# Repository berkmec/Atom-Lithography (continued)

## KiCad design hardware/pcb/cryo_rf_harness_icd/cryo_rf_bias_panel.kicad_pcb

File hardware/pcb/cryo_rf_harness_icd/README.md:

# Cryo-RF, Microwave, Quench & rf-SET Harness ICD (`hardware/pcb/cryo_rf_harness_icd/`)

> **Epistemic Status:** `M0_M1_DESIGN_ONLY` (`no_lab_measurement=true`, `no_physical_fab=true`, `iec61508_certified=false`, `semi_s2_certified=false`). All SPICE results below were executed live on rootless `ngspice-47`.

## 1. Scope (`17 E2` Parts + `S6.3-04` Quench Harness)
- **E2 Parts (`17`):** `S3.2-04, S6.4-03, S6.5-03, S6.6-01, S6.6-02, S6.6-03, S6.6-04, S6.6-07, S6.7-01, S6.10-01, S6.11-02, S6.11-03, S6.11-04, S9.3-02, S9.4-01, S9.4-02, S9.4-03`
- **Magnet Quench Harness (`1`):** `S6.3-04` (with `S7.SAFETY-05` external `1.563 Ohm` dump bank)

## 2. KiCad 8 Bulkhead Distribution PCB (`cryo_rf_bias_panel`)
- **Stackup:** 4-layer Rogers RO4350B (`er=3.48`, `0.254 mm` outer cores), `170 x 120 mm`
- **Verification:** **`0` ERC errors**, **`0` ERC warnings**, **`0` DRC errors**, SCH/PCB parity = **`True`**, **`routed_net_count = 67/67`**, **`unrouted_net_count = 0`**, **`unconnected_items = 0`**, **`track_dangling_count = 0`** (`316` segments, `95` vias)
- **Contents:** `115` components, `67` nets: `8x` 4 K InP HEMT bias channels, `4x` 20 mK TWPA flux-bias + Eccosorb CR-124 LPF lanes, `4x` `50.00 Ohm` controlled-impedance Rogers RO4350B RF/rf-SET bias-tee monitor lanes (`8` Z0 checks PASS), and `S6.3-04` `400 V` quench voltage-tap isolation bay protected by a `2.5 x 92 mm` milled `Edge.Cuts` air-slot (`1` HV checks PASS).

## 3. Live `ngspice-47` Simulation Verification
| Deck | BOM ID | Key Measured Metrics | Cross-Check Parity | Verdict |
|---|---|---|---|---|
| `qram_chebyshev_50_to_3k.cir` | `S9.4-02` | `max |S11|(4-8 GHz) = -24.4482 dB` (`<= -20 dB`), `min |S21| = -0.016282 dB` (`> -0.2 dB`), `BW(-20 dB) = 4.5181 GHz` (`3.7412-8.2592 GHz`) | Exact ABCD `|dS11| = 0.0 dB` | **PASS** |
| `magnet_quench_dump_1p563ohm.cir` | `S6.3-04` | `V_peak = 398.746 V` (`<= 400 V`), `tau = 0.37023 s` (`~0.370 s`), `E_dump = 18.8243 / 18.9408 kJ` (**`99.385% >= 99%`**), `T_dump_peak = 38.06 C` | Analytical LR `|dtau| = 0.011%` | **PASS** |
| `rf_set_tank_biastee.cir` | `S6.7-01` | `f_res = 321.0 MHz` (`250-400 MHz`), `|Gamma(50k)| = 0.07782`, `|Gamma(200k)| = 0.48068`, `Delta|Gamma| = 0.40286`, DC-bias RF isolation = **`113.57 dB`** (worst `200-450 MHz`: `98.69 dB > 40 dB`) | Python MNA `|dGamma| = 0.0` | **PASS** |

## 4. 6-Stage Thermal & Attenuation Reconciliation (`Exp125` / `Exp140` / `Exp142`)
- **Staged RF Input Attenuation:** `-20 dB (4 K) / -10 dB (800 mK Still) / -10 dB (100 mK CP) / -20 dB (20 mK MXC)` (`-60 dB` total, cascaded `n_th(6 GHz, 20 mK) = 0.00505`).
- **Combined M4 `1,024`-Cell (`Exp140`) + Option-Q (`Exp142`) Cryo Loads:**
  - `20 mK (MXC)`: **`7.036 uW`** (`<= 14.0 uW` LD400 cap)
  - `100 mK (CP)`: **`65.73 uW`** (`<= 400.0 uW` cap)
  - `800 mK (Still)`: **`1.09 mW`** (`<= 40.0 mW` cap)
  - `4 K`: **`0.55 W`** (`<= 2.0 W` PT420 cap)
  - `50 K`: **`8.74 W`** (`<= 40.0 W` / `55.0 W` PT420 cap)

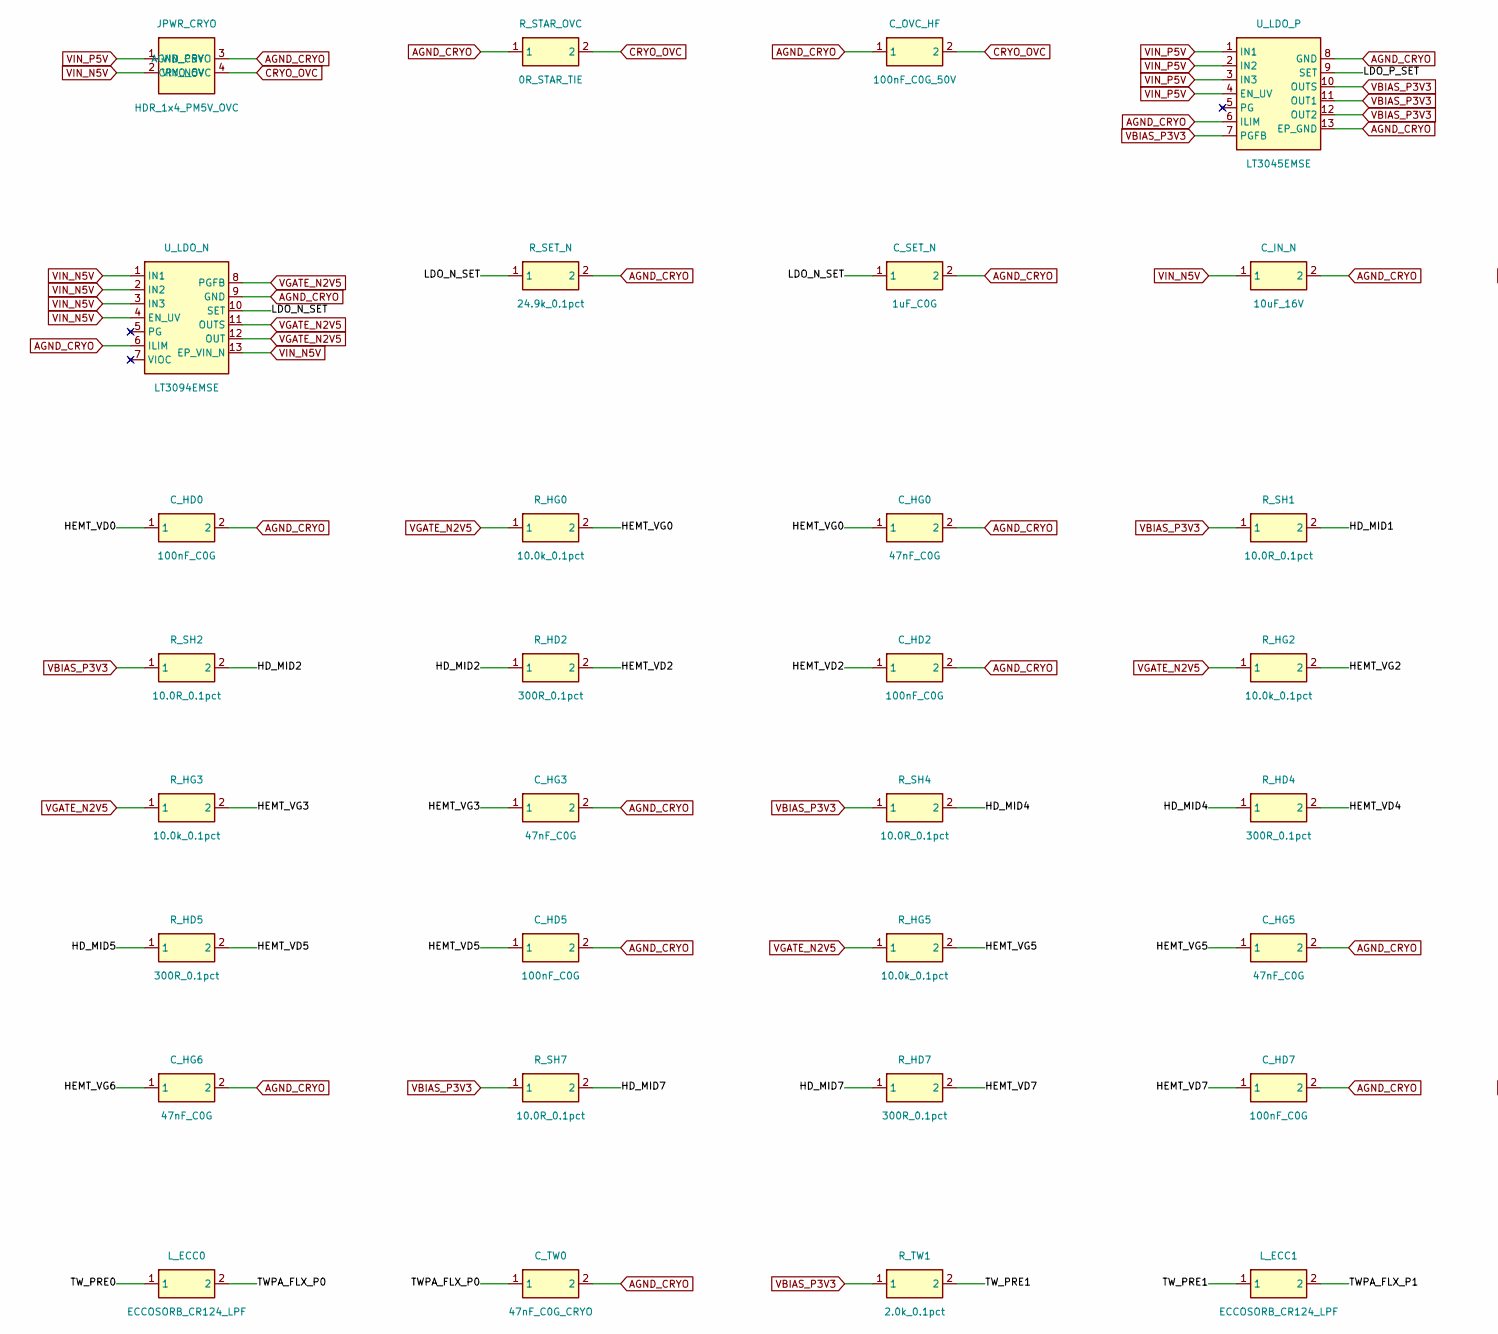
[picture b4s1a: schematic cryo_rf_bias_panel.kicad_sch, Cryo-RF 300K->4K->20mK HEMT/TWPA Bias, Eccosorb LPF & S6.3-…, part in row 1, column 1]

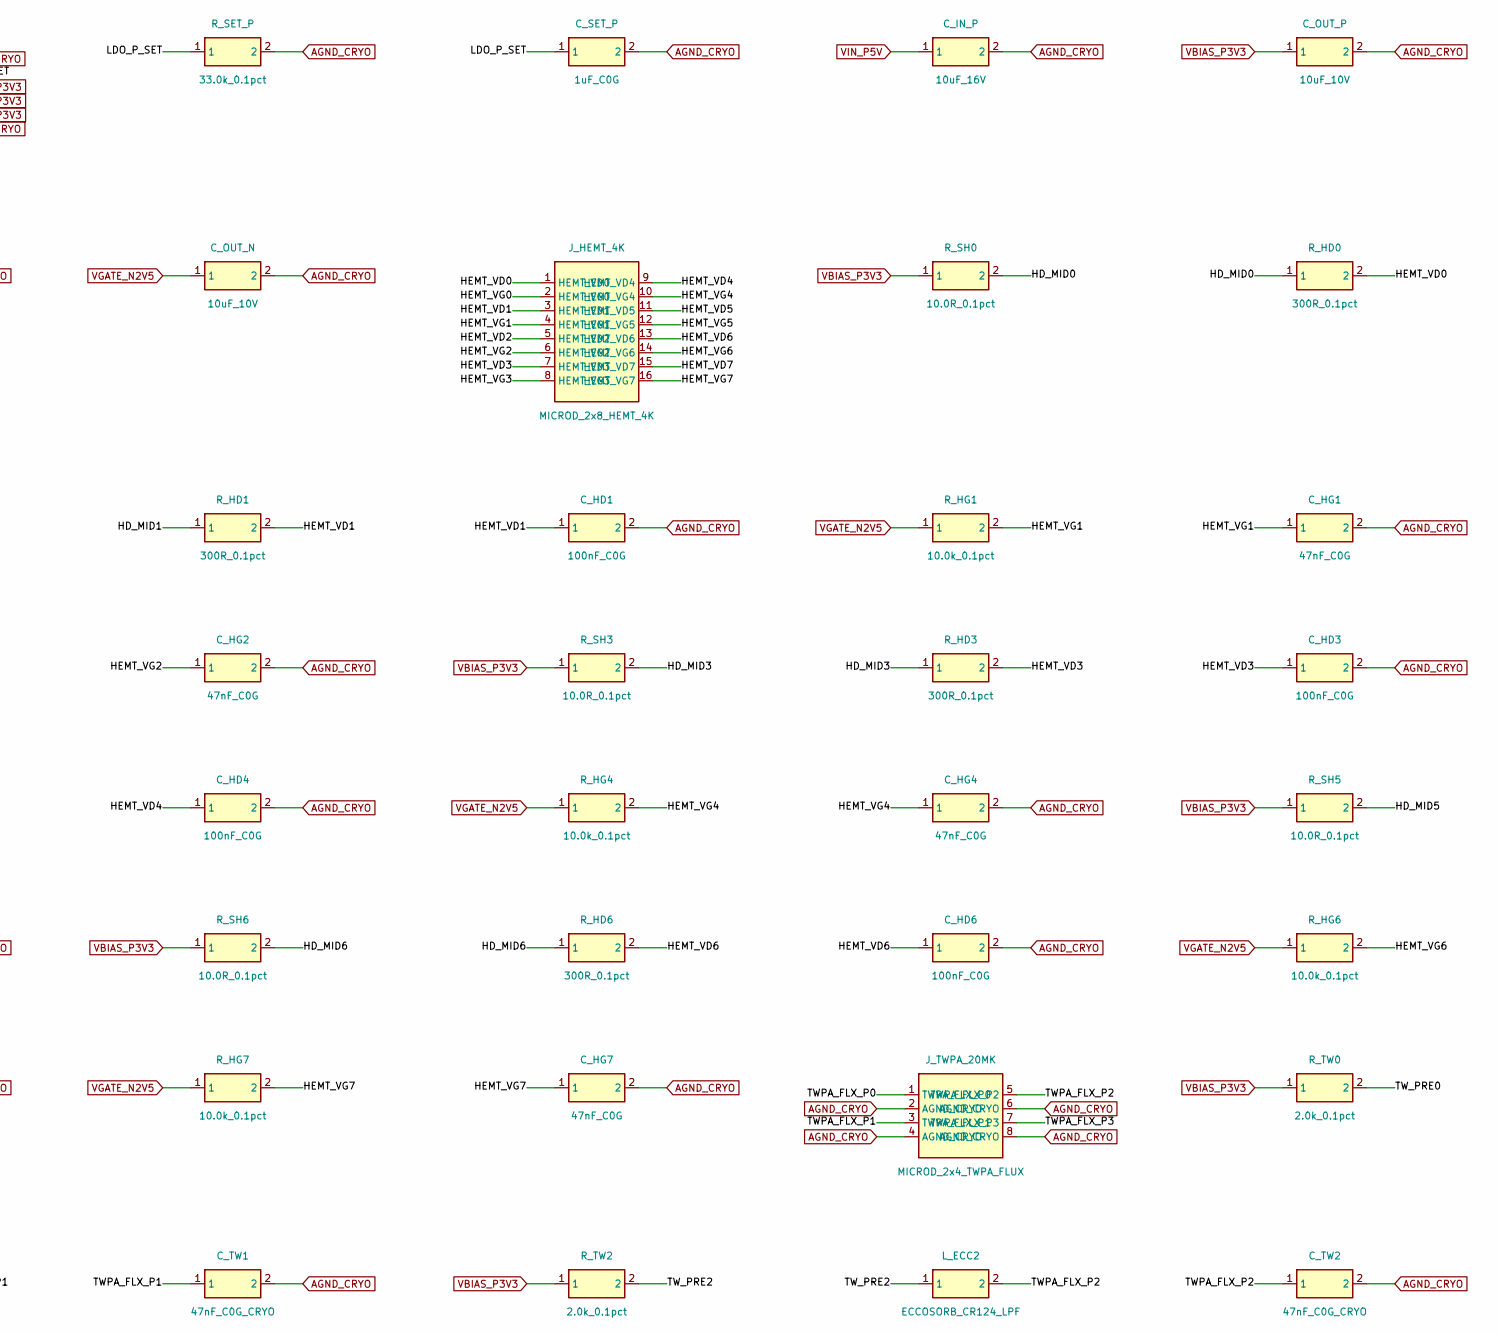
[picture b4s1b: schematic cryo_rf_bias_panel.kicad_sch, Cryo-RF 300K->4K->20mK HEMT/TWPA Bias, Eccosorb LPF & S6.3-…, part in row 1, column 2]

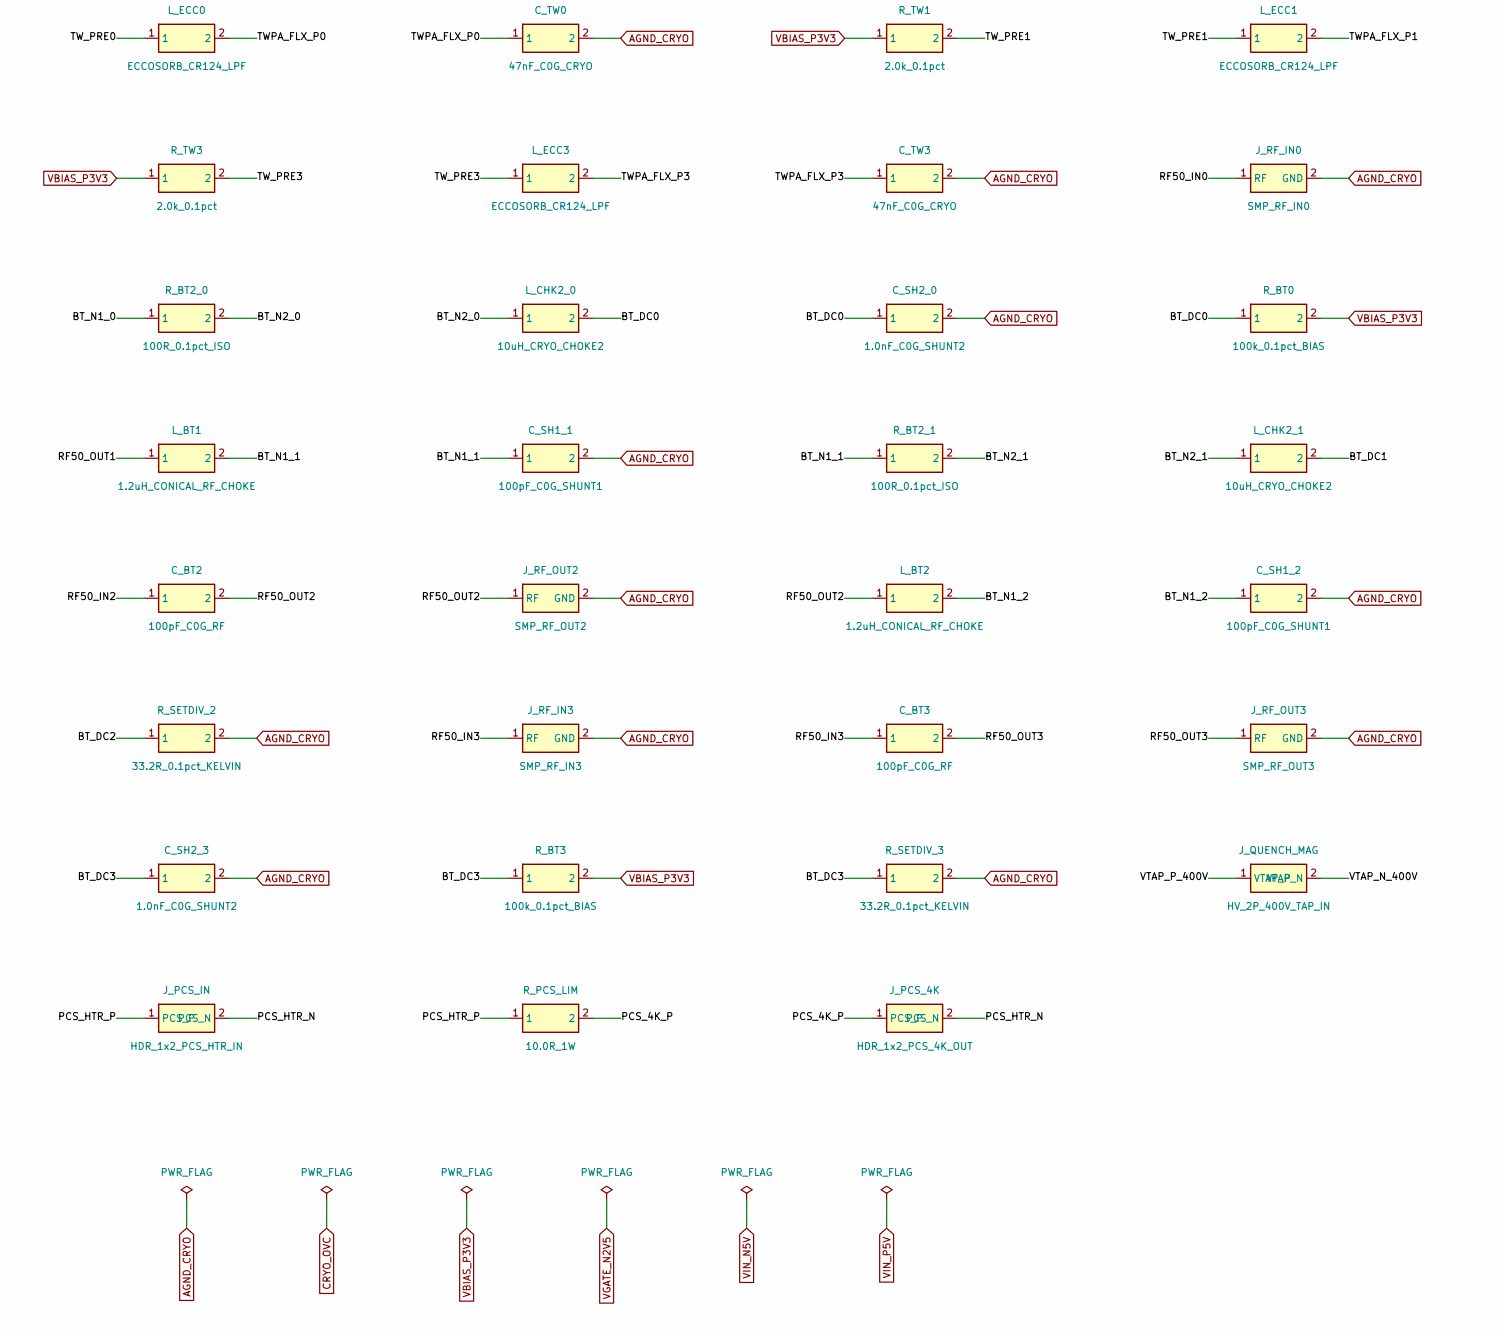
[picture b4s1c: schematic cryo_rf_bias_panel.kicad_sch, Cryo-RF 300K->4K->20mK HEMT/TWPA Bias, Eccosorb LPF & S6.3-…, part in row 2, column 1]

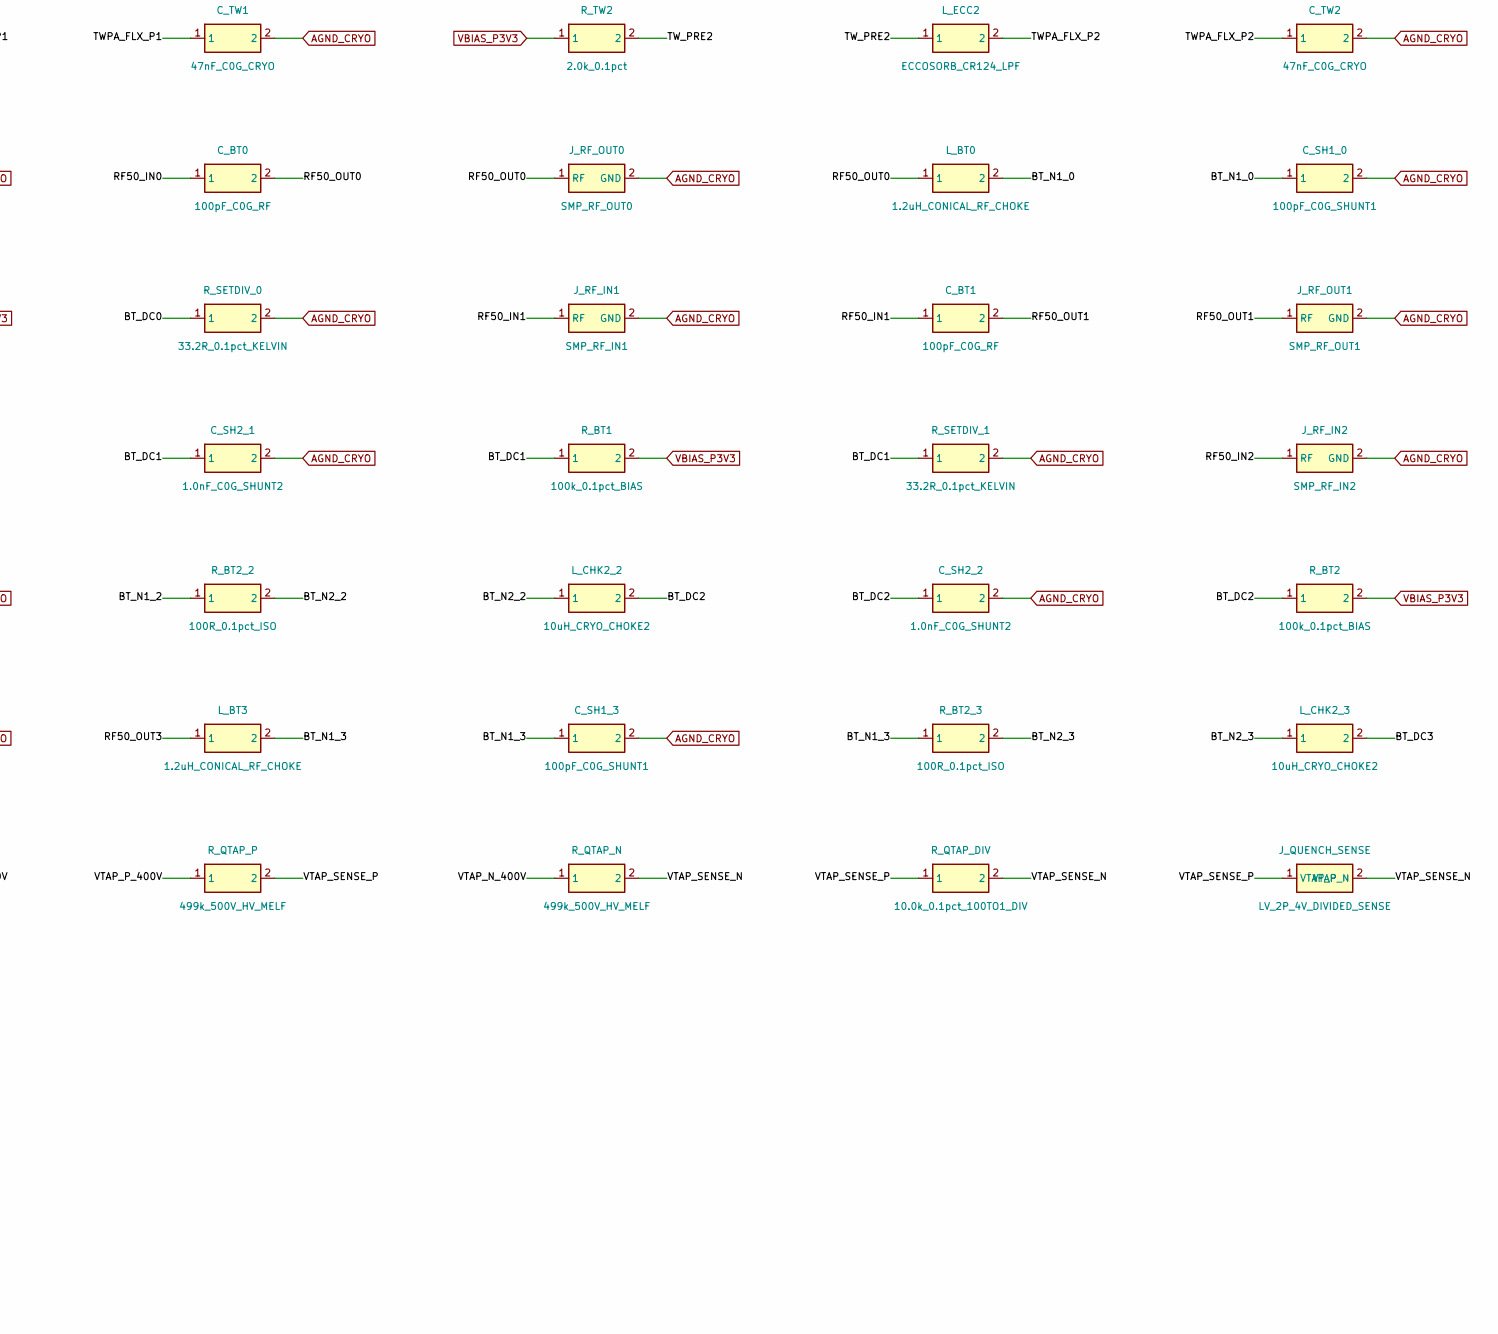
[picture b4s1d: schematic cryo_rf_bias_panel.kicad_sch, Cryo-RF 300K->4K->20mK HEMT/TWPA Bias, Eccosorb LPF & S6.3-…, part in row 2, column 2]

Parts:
C_BT0, C_BT1, C_BT2, C_BT3: 100pF_C0G_RF; C_0603_1608Metric; MPN 600S101FT250XT
C_HD0, C_HD1, C_HD2, C_HD3, C_HD4, C_HD5, C_HD6, C_HD7: 100nF_C0G; C_0603_1608Metric; MPN C0603C104J5GEC
C_HG0, C_HG1, C_HG2, C_HG3, C_HG4, C_HG5, C_HG6, C_HG7: 47nF_C0G; C_0603_1608Metric; MPN C0603C473J5GEC
C_IN_N: 10uF_16V; C_0805_2012Metric; MPN C0805C106K4PAC
C_IN_P: 10uF_16V; C_0805_2012Metric; MPN C0805C106K4PAC
C_OUT_N: 10uF_10V; C_0805_2012Metric; MPN C0805C106K8PAC
C_OUT_P: 10uF_10V; C_0805_2012Metric; MPN C0805C106K8PAC
C_OVC_HF: 100nF_C0G_50V; C_0805_2012Metric; MPN C0805C104J5GEC
C_SET_N: 1uF_C0G; C_0805_2012Metric; MPN C0805C105K5RAC
C_SET_P: 1uF_C0G; C_0805_2012Metric; MPN C0805C105K5RAC
C_SH1_0, C_SH1_1, C_SH1_2, C_SH1_3: 100pF_C0G_SHUNT1; C_0402_1005Metric; MPN 600L101FT200T
C_SH2_0, C_SH2_1, C_SH2_2, C_SH2_3: 1.0nF_C0G_SHUNT2; C_0402_1005Metric; MPN C0402C102J5GEC
C_TW0, C_TW1, C_TW2, C_TW3: 47nF_C0G_CRYO; C_0603_1608Metric; MPN C0603C473J5GEC
JPWR_CRYO: HDR_1x4_PM5V_OVC; HDR_1x4_2.54mm; MPN MicroD-4P-Cryo
J_HEMT_4K: MICROD_2x8_HEMT_4K; HDR_2x8_2.54mm; MPN MDM-16SH003B-Cryo
J_PCS_4K: HDR_1x2_PCS_4K_OUT; HDR_1x2_2.54mm; MPN MDM-2P-Cryo
J_PCS_IN: HDR_1x2_PCS_HTR_IN; HDR_1x2_2.54mm; MPN LEMO-EGG-0B-302
J_QUENCH_MAG: HV_2P_400V_TAP_IN; HV_1x2_7.62mm; MPN 1757019-HV-762
J_QUENCH_SENSE: LV_2P_4V_DIVIDED_SENSE; HV_1x2_7.62mm; MPN 1757019-HV-762
J_RF_IN0: SMP_RF_IN0; SMP_Cryo_50R; MPN SMP-MSLD-PCT-50
J_RF_IN1: SMP_RF_IN1; SMP_Cryo_50R; MPN SMP-MSLD-PCT-50
J_RF_IN2: SMP_RF_IN2; SMP_Cryo_50R; MPN SMP-MSLD-PCT-50
J_RF_IN3: SMP_RF_IN3; SMP_Cryo_50R; MPN SMP-MSLD-PCT-50
J_RF_OUT0: SMP_RF_OUT0; SMP_Cryo_50R; MPN SMP-MSLD-PCT-50
J_RF_OUT1: SMP_RF_OUT1; SMP_Cryo_50R; MPN SMP-MSLD-PCT-50
J_RF_OUT2: SMP_RF_OUT2; SMP_Cryo_50R; MPN SMP-MSLD-PCT-50
J_RF_OUT3: SMP_RF_OUT3; SMP_Cryo_50R; MPN SMP-MSLD-PCT-50
J_TWPA_20MK: MICROD_2x4_TWPA_FLUX; HDR_2x4_2.54mm; MPN MDM-9SH003B-NbTi
L_BT0, L_BT1, L_BT2, L_BT3: 1.2uH_CONICAL_RF_CHOKE; L_0603_1608Metric; MPN CC45T44K240G5
L_CHK2_0, L_CHK2_1, L_CHK2_2, L_CHK2_3: 10uH_CRYO_CHOKE2; L_0603_1608Metric; MPN 0603CS-103XJL
L_ECC0, L_ECC1, L_ECC2, L_ECC3: ECCOSORB_CR124_LPF; L_1206_3216Metric; MPN ECCOSORB-CR124-INLINE
R_BT0, R_BT1, R_BT2, R_BT3: 100k_0.1pct_BIAS; R_0402_1005Metric; MPN RT0402BRD07100KL
R_BT2_0, R_BT2_1, R_BT2_2, R_BT2_3: 100R_0.1pct_ISO; R_0402_1005Metric; MPN RT0402BRD07100RL
R_HD0, R_HD1, R_HD2, R_HD3, R_HD4, R_HD5, R_HD6, R_HD7: 300R_0.1pct; R_0603_1608Metric; MPN RT0603BRD07300RL
R_HG0, R_HG1, R_HG2, R_HG3, R_HG4, R_HG5, R_HG6, R_HG7: 10.0k_0.1pct; R_0603_1608Metric; MPN RT0603BRD0710KL
R_PCS_LIM: 10.0R_1W; R_1206_3216Metric; MPN CRCW120610R0FKEA
R_QTAP_DIV: 10.0k_0.1pct_100TO1_DIV; R_0805_2012Metric; MPN RT0805BRD0710KL
R_QTAP_N: 499k_500V_HV_MELF; R_HV_MELF_500V_7mm; MPN HVCB2512FDC499K
R_QTAP_P: 499k_500V_HV_MELF; R_HV_MELF_500V_7mm; MPN HVCB2512FDC499K
R_SETDIV_0, R_SETDIV_1, R_SETDIV_2, R_SETDIV_3: 33.2R_0.1pct_KELVIN; R_0402_1005Metric; MPN RT0402BRD0733R2L
R_SET_N: 24.9k_0.1pct; R_0603_1608Metric; MPN RT0603BRD0724K9L
R_SET_P: 33.0k_0.1pct; R_0603_1608Metric; MPN RT0603BRD0733KL
R_SH0, R_SH1, R_SH2, R_SH3, R_SH4, R_SH5, R_SH6, R_SH7: 10.0R_0.1pct; R_0603_1608Metric; MPN RT0603BRD0710RL
R_STAR_OVC: 0R_STAR_TIE; R_0805_2012Metric; MPN CRCW08050000Z0EA
R_TW0, R_TW1, R_TW2, R_TW3: 2.0k_0.1pct; R_0603_1608Metric; MPN RT0603BRD072KL
U_LDO_N: LT3094EMSE; MSOP-12-1EP_3x4mm_P0.65mm; MPN LT3094EMSE
U_LDO_P: LT3045EMSE; MSOP-12-1EP_3x4mm_P0.65mm; MPN LT3045EMSE

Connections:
AGND_CRYO: C_HD0.2, C_HD1.2, C_HD2.2, C_HD3.2, C_HD4.2, C_HD5.2, C_HD6.2, C_HD7.2, C_HG0.2, C_HG1.2, C_HG2.2, C_HG3.2, C_HG4.2, C_HG5.2, C_HG6.2, C_HG7.2, C_IN_N.2, C_IN_P.2, C_OUT_N.2, C_OUT_P.2, C_OVC_HF.1, C_SET_N.2, C_SET_P.2, C_SH1_0.2, C_SH1_1.2, C_SH1_2.2, C_SH1_3.2, C_SH2_0.2, C_SH2_1.2, C_SH2_2.2, C_SH2_3.2, C_TW0.2, C_TW1.2, C_TW2.2, C_TW3.2, JPWR_CRYO.3 (AGND_CRYO), J_RF_IN0.2 (GND), J_RF_IN1.2 (GND), J_RF_IN2.2 (GND), J_RF_IN3.2 (GND), J_RF_OUT0.2 (GND), J_RF_OUT1.2 (GND), J_RF_OUT2.2 (GND), J_RF_OUT3.2 (GND), J_TWPA_20MK.2 (AGND_CRYO), J_TWPA_20MK.4 (AGND_CRYO), J_TWPA_20MK.6 (AGND_CRYO), J_TWPA_20MK.8 (AGND_CRYO), R_SETDIV_0.2, R_SETDIV_1.2, R_SETDIV_2.2, R_SETDIV_3.2, R_SET_N.2, R_SET_P.2, R_STAR_OVC.1, U_LDO_N.6 (ILIM), U_LDO_N.9 (GND), U_LDO_P.6 (ILIM), U_LDO_P.8 (GND), U_LDO_P.13 (EP_GND)
BT_DC0: C_SH2_0.1, L_CHK2_0.2, R_BT0.1, R_SETDIV_0.1
BT_DC1: C_SH2_1.1, L_CHK2_1.2, R_BT1.1, R_SETDIV_1.1
BT_DC2: C_SH2_2.1, L_CHK2_2.2, R_BT2.1, R_SETDIV_2.1
BT_DC3: C_SH2_3.1, L_CHK2_3.2, R_BT3.1, R_SETDIV_3.1
BT_N1_0: C_SH1_0.1, L_BT0.2, R_BT2_0.1
BT_N1_1: C_SH1_1.1, L_BT1.2, R_BT2_1.1
BT_N1_2: C_SH1_2.1, L_BT2.2, R_BT2_2.1
BT_N1_3: C_SH1_3.1, L_BT3.2, R_BT2_3.1
BT_N2_0: L_CHK2_0.1, R_BT2_0.2
BT_N2_1: L_CHK2_1.1, R_BT2_1.2
BT_N2_2: L_CHK2_2.1, R_BT2_2.2
BT_N2_3: L_CHK2_3.1, R_BT2_3.2
CRYO_OVC: C_OVC_HF.2, JPWR_CRYO.4 (CRYO_OVC), R_STAR_OVC.2
HD_MID0: R_HD0.1, R_SH0.2
HD_MID1: R_HD1.1, R_SH1.2
HD_MID2: R_HD2.1, R_SH2.2
HD_MID3: R_HD3.1, R_SH3.2
HD_MID4: R_HD4.1, R_SH4.2
HD_MID5: R_HD5.1, R_SH5.2
HD_MID6: R_HD6.1, R_SH6.2
HD_MID7: R_HD7.1, R_SH7.2
HEMT_VD0: C_HD0.1, J_HEMT_4K.1 (HEMT_VD0), R_HD0.2
HEMT_VD1: C_HD1.1, J_HEMT_4K.3 (HEMT_VD1), R_HD1.2
HEMT_VD2: C_HD2.1, J_HEMT_4K.5 (HEMT_VD2), R_HD2.2
HEMT_VD3: C_HD3.1, J_HEMT_4K.7 (HEMT_VD3), R_HD3.2
HEMT_VD4: C_HD4.1, J_HEMT_4K.9 (HEMT_VD4), R_HD4.2
HEMT_VD5: C_HD5.1, J_HEMT_4K.11 (HEMT_VD5), R_HD5.2
HEMT_VD6: C_HD6.1, J_HEMT_4K.13 (HEMT_VD6), R_HD6.2
HEMT_VD7: C_HD7.1, J_HEMT_4K.15 (HEMT_VD7), R_HD7.2
HEMT_VG0: C_HG0.1, J_HEMT_4K.2 (HEMT_VG0), R_HG0.2
HEMT_VG1: C_HG1.1, J_HEMT_4K.4 (HEMT_VG1), R_HG1.2
HEMT_VG2: C_HG2.1, J_HEMT_4K.6 (HEMT_VG2), R_HG2.2
HEMT_VG3: C_HG3.1, J_HEMT_4K.8 (HEMT_VG3), R_HG3.2
HEMT_VG4: C_HG4.1, J_HEMT_4K.10 (HEMT_VG4), R_HG4.2
HEMT_VG5: C_HG5.1, J_HEMT_4K.12 (HEMT_VG5), R_HG5.2
HEMT_VG6: C_HG6.1, J_HEMT_4K.14 (HEMT_VG6), R_HG6.2
HEMT_VG7: C_HG7.1, J_HEMT_4K.16 (HEMT_VG7), R_HG7.2
LDO_N_SET: C_SET_N.1, R_SET_N.1, U_LDO_N.10 (SET)
LDO_P_SET: C_SET_P.1, R_SET_P.1, U_LDO_P.9 (SET)
PCS_4K_P: J_PCS_4K.1 (PCS_P), R_PCS_LIM.2
PCS_HTR_N: J_PCS_4K.2 (PCS_N), J_PCS_IN.2 (PCS_N)
PCS_HTR_P: J_PCS_IN.1 (PCS_P), R_PCS_LIM.1
RF50_IN0: C_BT0.1, J_RF_IN0.1 (RF)
RF50_IN1: C_BT1.1, J_RF_IN1.1 (RF)
RF50_IN2: C_BT2.1, J_RF_IN2.1 (RF)
RF50_IN3: C_BT3.1, J_RF_IN3.1 (RF)
RF50_OUT0: C_BT0.2, J_RF_OUT0.1 (RF), L_BT0.1
RF50_OUT1: C_BT1.2, J_RF_OUT1.1 (RF), L_BT1.1
RF50_OUT2: C_BT2.2, J_RF_OUT2.1 (RF), L_BT2.1
RF50_OUT3: C_BT3.2, J_RF_OUT3.1 (RF), L_BT3.1
TWPA_FLX_P0: C_TW0.1, J_TWPA_20MK.1 (TWPA_FLX_P0), L_ECC0.2
TWPA_FLX_P1: C_TW1.1, J_TWPA_20MK.3 (TWPA_FLX_P1), L_ECC1.2
TWPA_FLX_P2: C_TW2.1, J_TWPA_20MK.5 (TWPA_FLX_P2), L_ECC2.2
TWPA_FLX_P3: C_TW3.1, J_TWPA_20MK.7 (TWPA_FLX_P3), L_ECC3.2
TW_PRE0: L_ECC0.1, R_TW0.2
TW_PRE1: L_ECC1.1, R_TW1.2
TW_PRE2: L_ECC2.1, R_TW2.2
TW_PRE3: L_ECC3.1, R_TW3.2
VBIAS_P3V3: C_OUT_P.1, R_BT0.2, R_BT1.2, R_BT2.2, R_BT3.2, R_SH0.1, R_SH1.1, R_SH2.1, R_SH3.1, R_SH4.1, R_SH5.1, R_SH6.1, R_SH7.1, R_TW0.1, R_TW1.1, R_TW2.1, R_TW3.1, U_LDO_P.7 (PGFB), U_LDO_P.10 (OUTS), U_LDO_P.11 (OUT1), U_LDO_P.12 (OUT2)
VGATE_N2V5: C_OUT_N.1, R_HG0.1, R_HG1.1, R_HG2.1, R_HG3.1, R_HG4.1, R_HG5.1, R_HG6.1, R_HG7.1, U_LDO_N.8 (PGFB), U_LDO_N.11 (OUTS), U_LDO_N.12 (OUT)
VIN_N5V: C_IN_N.1, JPWR_CRYO.2 (VIN_N5V), U_LDO_N.1 (IN1), U_LDO_N.2 (IN2), U_LDO_N.3 (IN3), U_LDO_N.4 (EN_UV), U_LDO_N.13 (EP_VIN_N)
VIN_P5V: C_IN_P.1, JPWR_CRYO.1 (VIN_P5V), U_LDO_P.1 (IN1), U_LDO_P.2 (IN2), U_LDO_P.3 (IN3), U_LDO_P.4 (EN_UV)
VTAP_N_400V: J_QUENCH_MAG.2 (VTAP_N), R_QTAP_N.1
VTAP_P_400V: J_QUENCH_MAG.1 (VTAP_P), R_QTAP_P.1
VTAP_SENSE_N: J_QUENCH_SENSE.2 (VTAP_N), R_QTAP_DIV.2, R_QTAP_N.2
VTAP_SENSE_P: J_QUENCH_SENSE.1 (VTAP_P), R_QTAP_DIV.1, R_QTAP_P.2

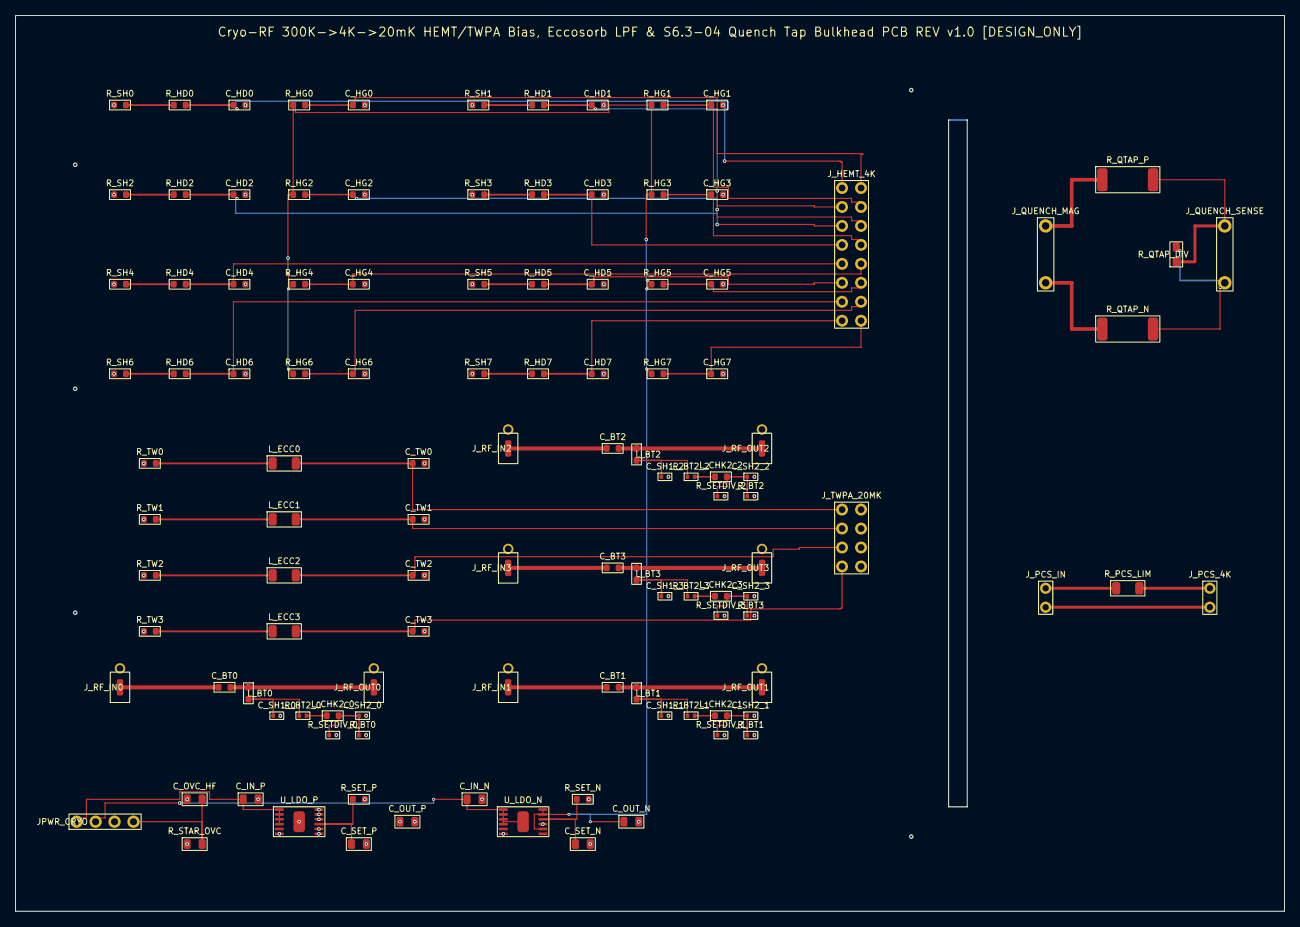
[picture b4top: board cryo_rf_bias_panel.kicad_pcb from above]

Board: 4 copper layers, 170.0 x 120.0 mm, 115 parts (0 on the bottom side), 67 nets.
